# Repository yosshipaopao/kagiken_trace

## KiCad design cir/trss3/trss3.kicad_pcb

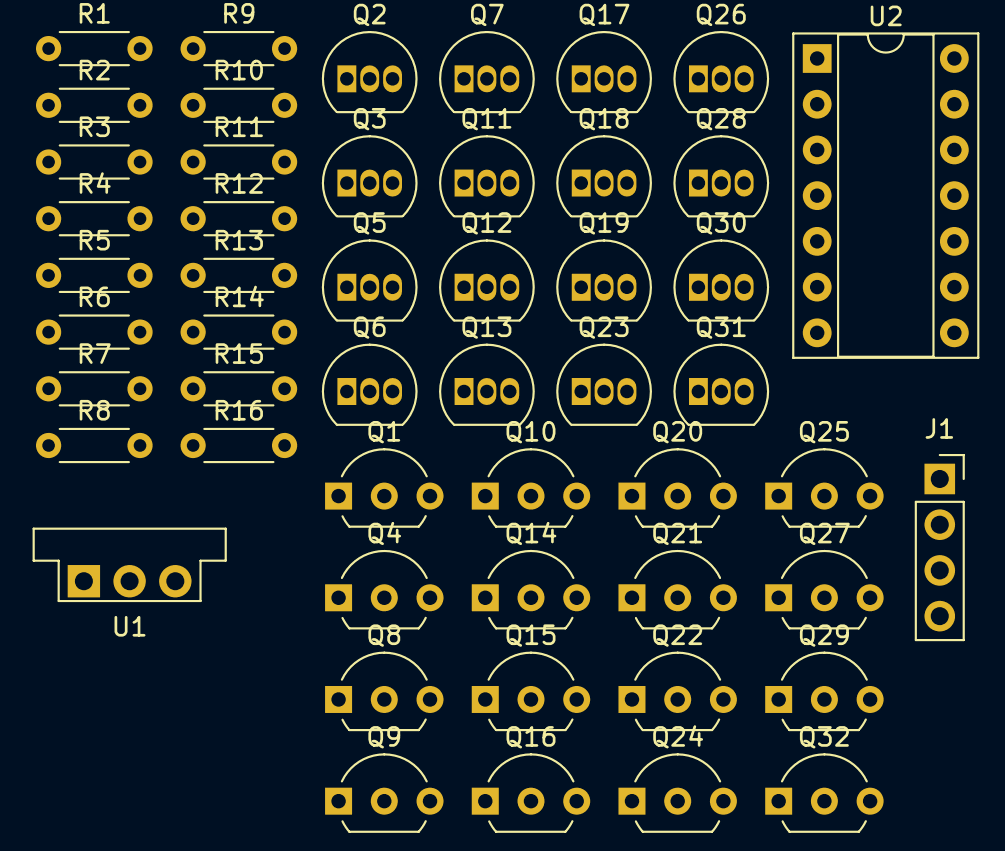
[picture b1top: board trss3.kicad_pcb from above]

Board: 2 copper layers, 51 parts (0 on the bottom side), 40 nets, no tracks yet.

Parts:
J1: Conn_01x04; PinSocket_1x04_P2.54mm_Vertical
Q1, Q4, Q8, Q9, Q10, Q14, Q15, Q16, Q20, Q21, Q22, Q24, Q25, Q27, Q29, Q32: 2SC1815; TO-92L_Inline_Wide
Q2, Q3, Q5, Q6, Q7, Q11, Q12, Q13, Q17, Q18, Q19, Q23, Q26, Q28, Q30, Q31: 2SA1015; TO-92_Inline
R1, R2, R3, R4, R5, R6, R7, R8: 10k; R_Axial_DIN0204_L3.6mm_D1.6mm_P5.08mm_Horizontal
R9, R10, R11, R12, R13, R14, R15, R16: 5.1k; R_Axial_DIN0204_L3.6mm_D1.6mm_P5.08mm_Horizontal
U1: OKI-78SR-12_1.0-W36-C; Converter_DCDC_Murata_OKI-78SR_Vertical
U2: 74LS07; DIP-14_W7.62mm_Socket

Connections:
+5V: Q2.2 (C), Q4.2 (C), Q5.2 (C), Q7.2 (C), Q9.2 (C), Q10.2 (C), Q11.2 (C), Q13.2 (C), Q16.2 (C), Q17.2 (C), Q19.2 (C), Q21.2 (C), Q22.2 (C), Q23.2 (C), Q25.2 (C), Q26.2 (C), Q29.2 (C), Q31.2 (C), U1.3 (OUT), U2.14 (VCC)
A: Q2.3 (B), Q7.3 (B), Q13.3 (B), Q21.3 (B), Q26.3 (B), Q32.3 (B), R9.1
A_IN: J1.1, U2.1
B: Q8.3 (B), Q11.3 (B), Q24.3 (B), Q28.3 (B), R10.1
B_IN: J1.2, U2.3
C: Q3.3 (B), Q14.3 (B), Q20.3 (B), Q30.3 (B), R11.1
C_IN: J1.3, U2.5
D: Q9.3 (B), Q12.3 (B), Q19.3 (B), Q23.3 (B), Q27.3 (B), Q31.3 (B), R12.1
D_IN: J1.4, U2.9
E: Q1.3 (B), Q5.3 (B), Q17.3 (B), Q27.1 (E), Q28.1 (E), R7.1
F: Q6.3 (B), Q15.3 (B), Q18.3 (B), Q30.1 (E), Q32.1 (E), R8.1
GND: R1.2, R2.2, R3.2, R4.2, R5.2, R6.2, R7.2, R8.2, U1.2 (GND), U2.7 (GND)
ML0: Q4.1 (E), Q6.1 (E), Q8.1 (E), Q9.1 (E), R2.1, R16.2
ML1: Q10.1 (E), Q14.1 (E), R3.1
MR0: Q16.1 (E), Q18.1 (E), Q20.1 (E), Q21.1 (E), R5.1, R15.2
MR1: Q22.1 (E), Q24.1 (E), R6.1
unnamed: Q1.2 (C), Q3.1 (E)
unnamed: Q1.1 (E), R1.1, R13.2
unnamed: Q2.1 (E), Q3.2 (C)
unnamed: Q5.1 (E), Q6.2 (C)
unnamed: Q7.1 (E), Q8.2 (C)
unnamed: Q10.3 (B), R16.1
unnamed: Q11.1 (E), Q12.2 (C)
unnamed: Q12.1 (E), Q15.2 (C)
unnamed: Q13.1 (E), Q14.2 (C)
unnamed: Q15.1 (E), R4.1, R14.2
unnamed: Q17.1 (E), Q18.2 (C)
unnamed: Q19.1 (E), Q20.2 (C)
unnamed: Q22.3 (B), R15.1
unnamed: Q23.1 (E), Q24.2 (C)
unnamed: Q25.1 (E), Q28.2 (C)
unnamed: Q26.1 (E), Q27.2 (C)
unnamed: Q29.1 (E), Q30.2 (C)
unnamed: Q31.1 (E), Q32.2 (C)
unnamed: R9.2, U2.2
unnamed: R10.2, U2.4
unnamed: R11.2, U2.6
unnamed: R12.2, U2.8
~A~CE: Q4.3 (B), Q25.3 (B), R13.1
~B~DF: Q16.3 (B), Q29.3 (B), R14.1

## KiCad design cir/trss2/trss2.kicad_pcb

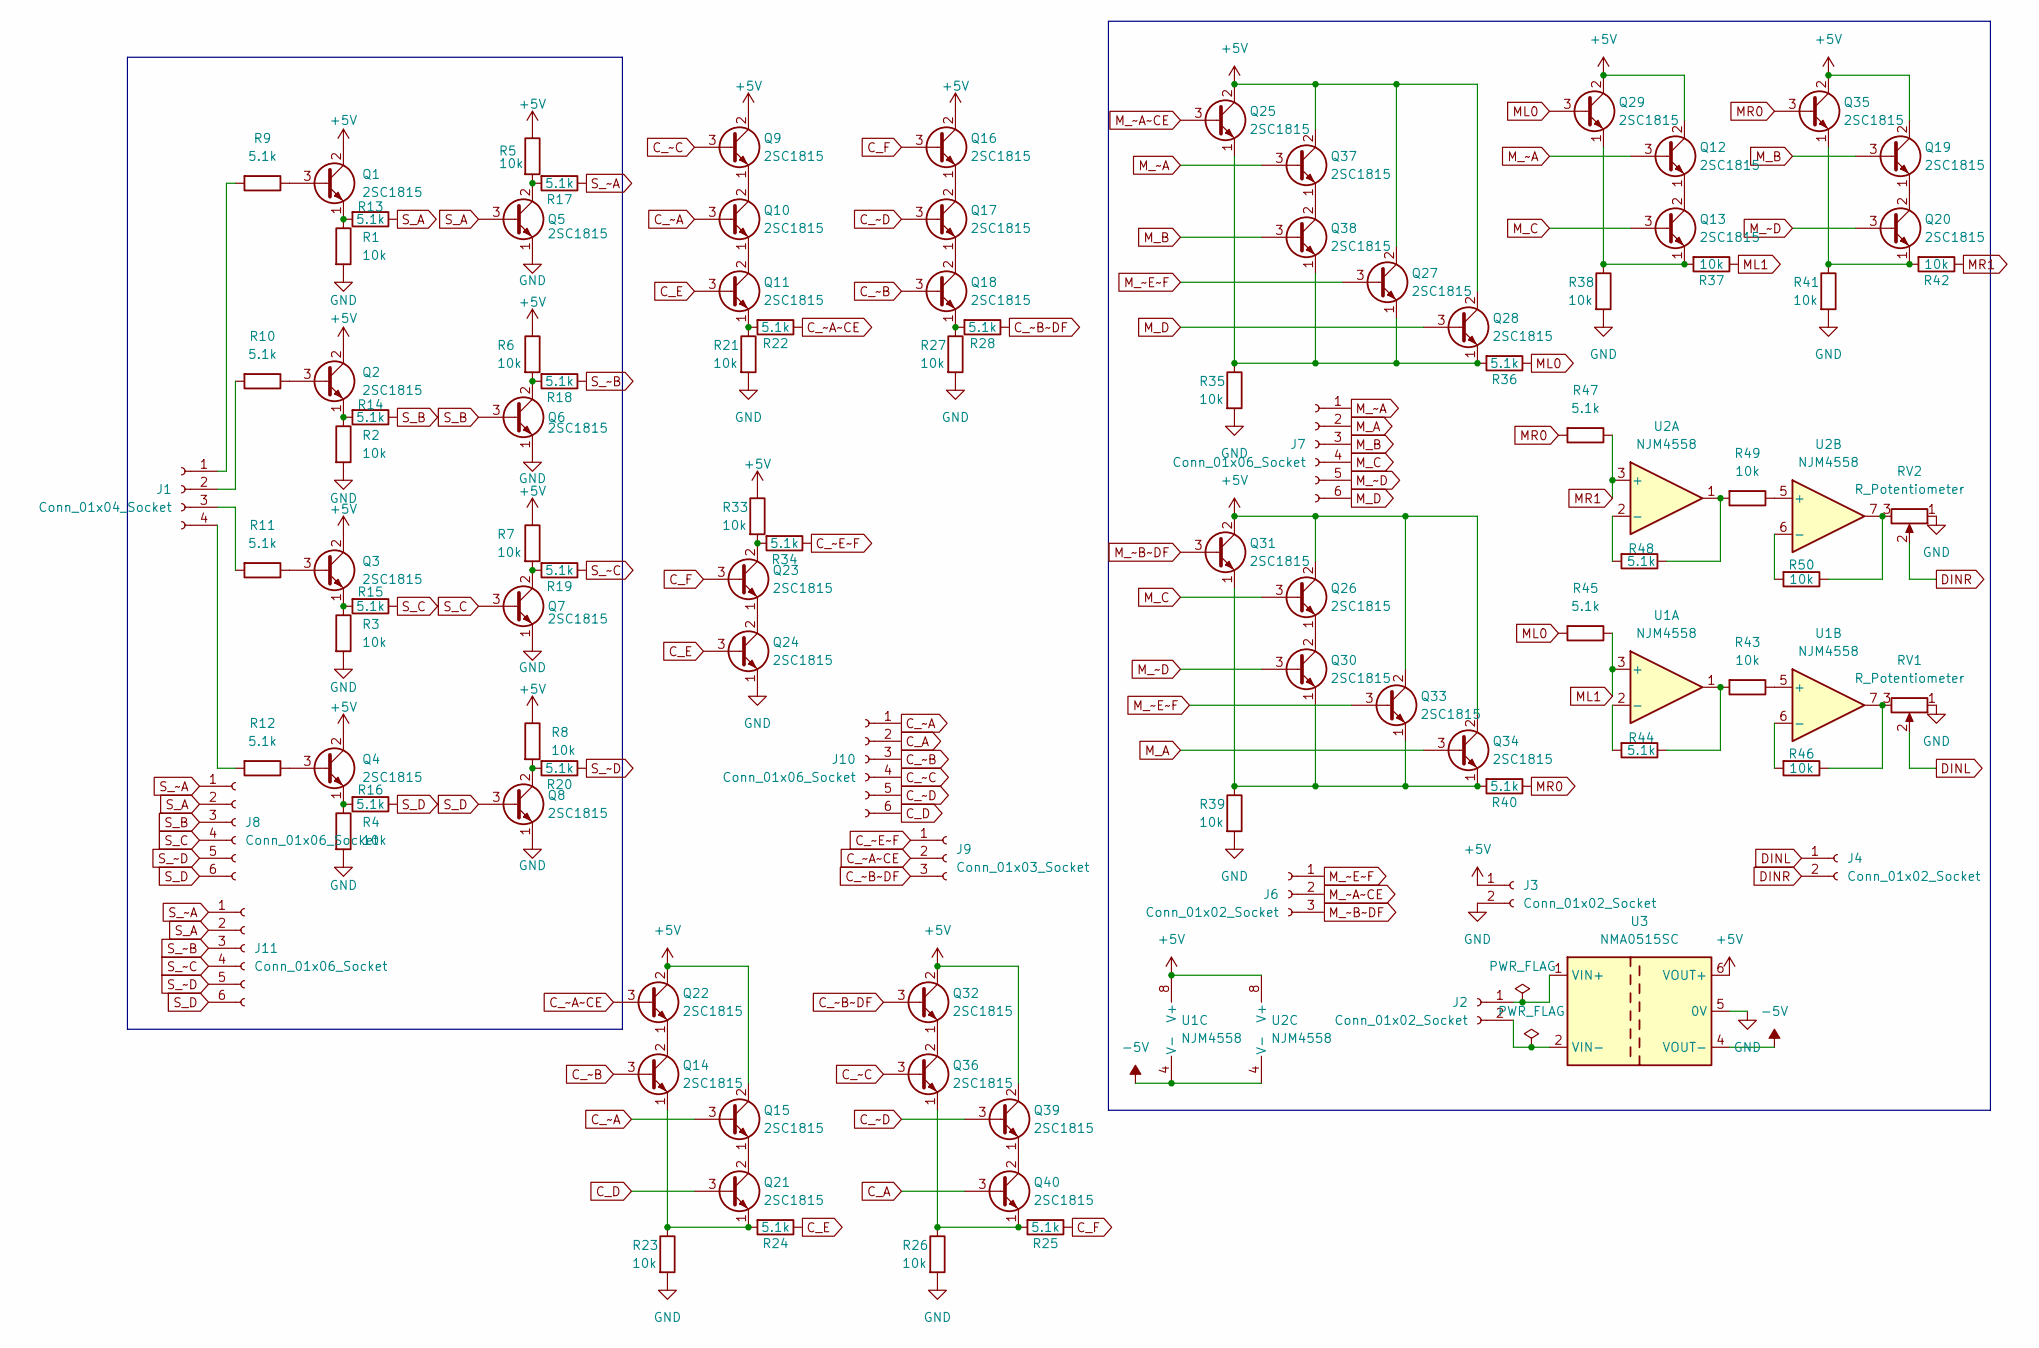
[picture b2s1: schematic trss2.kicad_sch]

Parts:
J1: Conn_01x04_Socket; PinSocket_1x04_P2.54mm_Vertical
J2, J3, J4: Conn_01x02_Socket; PinSocket_1x02_P2.54mm_Vertical
J6: Conn_01x02_Socket; PinSocket_1x03_P2.54mm_Vertical
J7, J8, J10, J11: Conn_01x06_Socket; PinSocket_1x06_P2.54mm_Vertical
J9: Conn_01x03_Socket; PinSocket_1x03_P2.54mm_Vertical
Q1, Q2, Q3, Q4, Q5, Q6, Q7, Q8, Q9, Q10, Q11, Q12, Q13, Q14, Q15, Q16, Q17, Q18, Q19, Q20, Q21, Q22, Q23, Q24, Q25, Q26, Q27, Q28, Q29, Q30, Q31, Q32, Q33, Q34, Q35, Q36, Q37, Q38, Q39, Q40: 2SC1815; TO-92_Inline_Wide
R1, R2, R3, R4, R5, R6, R7, R8, R21, R23, R26, R27, R33, R35, R37, R38, R39, R41, R42, R43, R46, R49, R50: 10k; R_Axial_DIN0204_L3.6mm_D1.6mm_P5.08mm_Horizontal
R9, R10, R11, R12, R17, R18, R19, R20, R22, R24, R25, R28, R34, R36, R40, R44, R45, R47, R48: 5.1k; R_Axial_DIN0204_L3.6mm_D1.6mm_P5.08mm_Horizontal
R13, R14, R15, R16: 5.1k; R_Axial_DIN0204_L3.6mm_D1.6mm_P7.62mm_Horizontal
RV1, RV2: R_Potentiometer; Potentiometer_Bourns_3296X_Horizontal
U1, U2: NJM4558; DIP-8_W7.62mm_Socket
U3: NMA0515SC; Converter_DCDC_Murata_NMAxxxxSC_THT

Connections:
+5V: J3.1, Q1.2 (C), Q2.2 (C), Q3.2 (C), Q4.2 (C), Q9.2 (C), Q12.2 (C), Q15.2 (C), Q16.2 (C), Q19.2 (C), Q22.2 (C), Q25.2 (C), Q26.2 (C), Q27.2 (C), Q28.2 (C), Q29.2 (C), Q31.2 (C), Q32.2 (C), Q33.2 (C), Q34.2 (C), Q35.2 (C), Q37.2 (C), Q39.2 (C), R5.1, R6.1, R7.1, R8.1, R33.1, U1.8 (V+), U2.8 (V+), U3.6 (VOUT+); also elsewhere on the board
-5V: U1.4 (V-), U2.4 (V-), U3.4 (VOUT-)
C_A: J10.2, Q40.3 (B); also elsewhere on the board
C_D: J10.6, Q21.3 (B); also elsewhere on the board
C_E: Q11.3 (B), Q24.3 (B), R24.1
C_F: Q16.3 (B), Q23.3 (B), R25.1
C_~A: J10.1, Q10.3 (B), Q15.3 (B); also elsewhere on the board
C_~A~CE: J9.2, Q22.3 (B), R22.1
C_~B: J10.3, Q14.3 (B), Q18.3 (B); also elsewhere on the board
C_~B~DF: J9.3, Q32.3 (B), R28.1
C_~C: J10.4, Q9.3 (B), Q36.3 (B); also elsewhere on the board
C_~D: J10.5, Q17.3 (B), Q39.3 (B); also elsewhere on the board
C_~E~F: J9.1, R34.1
DINL: J4.1, RV1.2
DINR: J4.2, RV2.2
GND: J3.2, Q5.1 (E), Q6.1 (E), Q7.1 (E), Q8.1 (E), Q24.1 (E), R1.2, R2.2, R3.2, R4.2, R21.2, R23.2, R26.2, R27.2, R35.2, R38.2, R39.2, R41.2, RV1.1, RV2.1, U3.5 (0V); also elsewhere on the board
ML0: Q29.3 (B), R36.1, R45.2
ML1: R37.1, R45.1, U1.3 (+)
MR0: Q35.3 (B), R40.1, R47.2
MR1: R42.1, R47.1, U2.3 (+)
M_A: J7.2, Q34.3 (B)
M_B: J7.3, Q19.3 (B), Q38.3 (B)
M_C: J7.4, Q13.3 (B), Q26.3 (B)
M_D: J7.6, Q28.3 (B)
M_~A: J7.1, Q12.3 (B), Q37.3 (B)
M_~A~CE: J6.2, Q25.3 (B)
M_~B~DF: J6.3, Q31.3 (B)
M_~D: J7.5, Q20.3 (B), Q30.3 (B)
M_~E~F: J6.1, Q27.3 (B), Q33.3 (B)
unnamed: J1.1, R9.2
unnamed: J1.2, R10.2
unnamed: J1.3, R11.2
unnamed: J1.4, R12.2
unnamed: J2.1, U3.1 (VIN+)
unnamed: J2.2, U3.2 (VIN-)
unnamed: Q1.3 (B), R9.1
unnamed: Q1.1 (E), R1.1, R13.2
unnamed: Q2.3 (B), R10.1
unnamed: Q2.1 (E), R2.1, R14.2
unnamed: Q3.3 (B), R11.1
unnamed: Q3.1 (E), R3.1, R15.2
unnamed: Q4.3 (B), R12.1
unnamed: Q4.1 (E), R4.1, R16.2
unnamed: Q5.2 (C), R5.2, R17.2
unnamed: Q6.2 (C), R6.2, R18.2
unnamed: Q7.2 (C), R7.2, R19.2
unnamed: Q8.2 (C), R8.2, R20.2
unnamed: Q9.1 (E), Q10.2 (C)
unnamed: Q10.1 (E), Q11.2 (C)
unnamed: Q11.1 (E), R21.1, R22.2
unnamed: Q12.1 (E), Q13.2 (C)
unnamed: Q13.1 (E), Q29.1 (E), R37.2, R38.1
unnamed: Q14.2 (C), Q22.1 (E)
unnamed: Q14.1 (E), Q21.1 (E), R23.1, R24.2
unnamed: Q15.1 (E), Q21.2 (C)
unnamed: Q16.1 (E), Q17.2 (C)
unnamed: Q17.1 (E), Q18.2 (C)
unnamed: Q18.1 (E), R27.1, R28.2
unnamed: Q19.1 (E), Q20.2 (C)
unnamed: Q20.1 (E), Q35.1 (E), R41.1, R42.2
unnamed: Q23.2 (C), R33.2, R34.2
unnamed: Q23.1 (E), Q24.2 (C)
unnamed: Q25.1 (E), Q27.1 (E), Q28.1 (E), Q38.1 (E), R35.1, R36.2
unnamed: Q26.1 (E), Q30.2 (C)
unnamed: Q30.1 (E), Q31.1 (E), Q33.1 (E), Q34.1 (E), R39.1, R40.2
unnamed: Q32.1 (E), Q36.2 (C)
unnamed: Q36.1 (E), Q40.1 (E), R25.2, R26.1
unnamed: Q37.1 (E), Q38.2 (C)
unnamed: Q39.1 (E), Q40.2 (C)
unnamed: R43.2, R44.1, U1.1
unnamed: R46.1, RV1.3, U1.7
unnamed: R48.1, R49.2, U2.1
unnamed: R50.1, RV2.3, U2.7
unnamed: R44.2, U1.2 (-)
unnamed: R43.1, U1.5 (+)
unnamed: R46.2, U1.6 (-)
unnamed: R48.2, U2.2 (-)
unnamed: R49.1, U2.5 (+)
unnamed: R50.2, U2.6 (-)
S_A: J8.2, J11.2, Q5.3 (B), R13.1
S_B: J8.3, Q6.3 (B), R14.1
S_C: J8.4, Q7.3 (B), R15.1
S_D: J8.6, J11.6, Q8.3 (B), R16.1
S_~A: J8.1, J11.1, R17.1
S_~B: J11.3, R18.1
S_~C: J11.4, R19.1
S_~D: J8.5, J11.5, R20.1

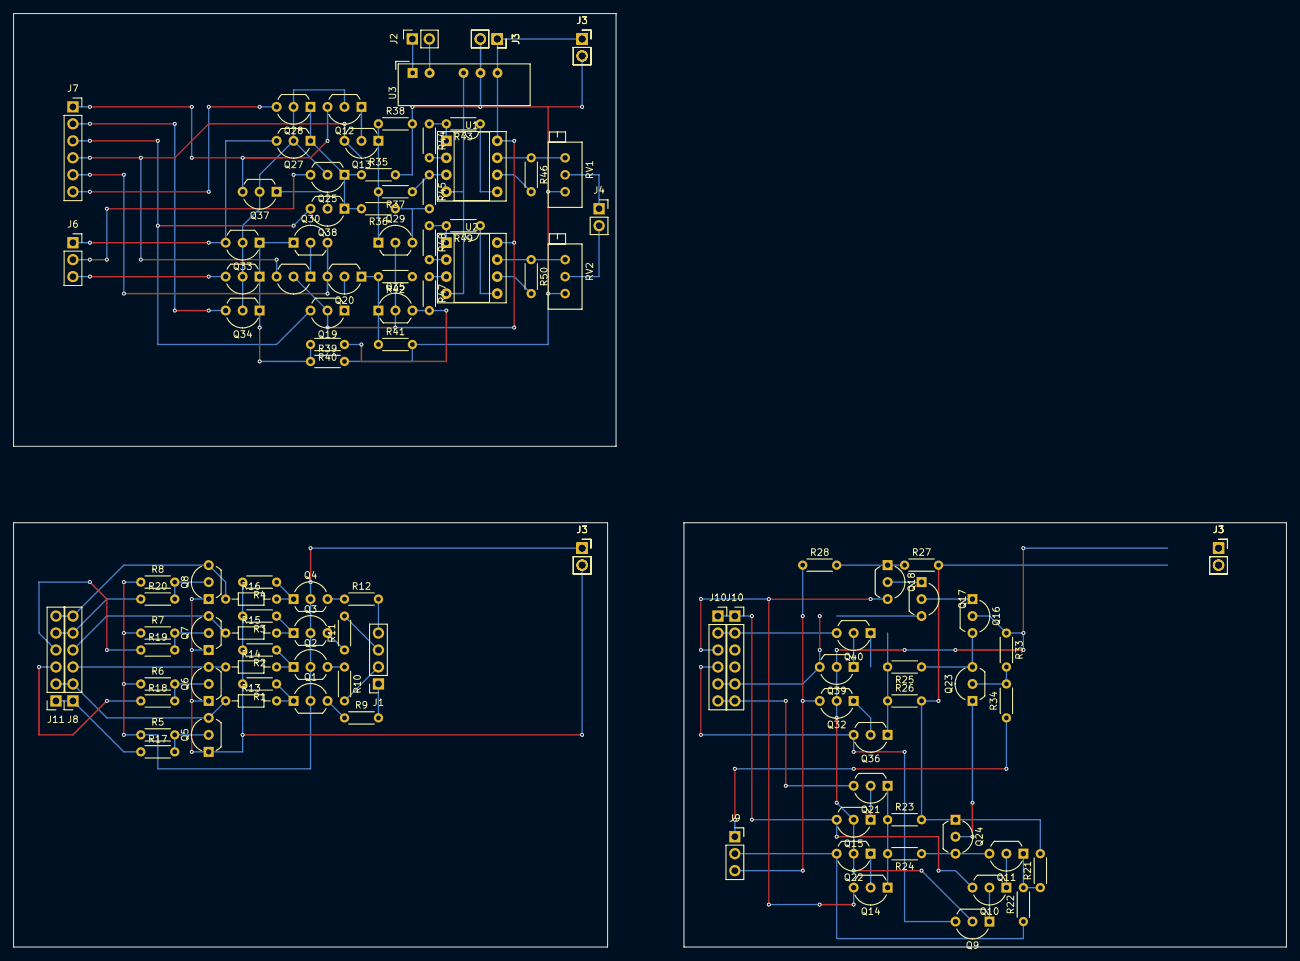
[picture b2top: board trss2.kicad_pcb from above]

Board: 2 copper layers, 190.5 x 139.7 mm, 109 parts (0 on the bottom side), 87 nets.

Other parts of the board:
J3#2, J3#3, J3#4, J3#5, J3#6, J3#7, J3#8: Conn_01x02_Socket; PinSocket_1x02_P2.54mm_Vertical
J10#2: Conn_01x06_Socket; PinSocket_1x06_P2.54mm_Vertical

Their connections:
+5V: J3#2.1, J3#3.1, J3#4.1, J3#5.1, J3#6.1, J3#7.1, J3#8.1; also elsewhere on the board
C_A: J10#2.2; also elsewhere on the board
C_D: J10#2.6; also elsewhere on the board
C_~A: J10#2.1; also elsewhere on the board
C_~B: J10#2.3; also elsewhere on the board
C_~C: J10#2.4; also elsewhere on the board
C_~D: J10#2.5; also elsewhere on the board
GND: J3#2.2, J3#3.2, J3#4.2, J3#5.2, J3#6.2, J3#7.2, J3#8.2; also elsewhere on the board

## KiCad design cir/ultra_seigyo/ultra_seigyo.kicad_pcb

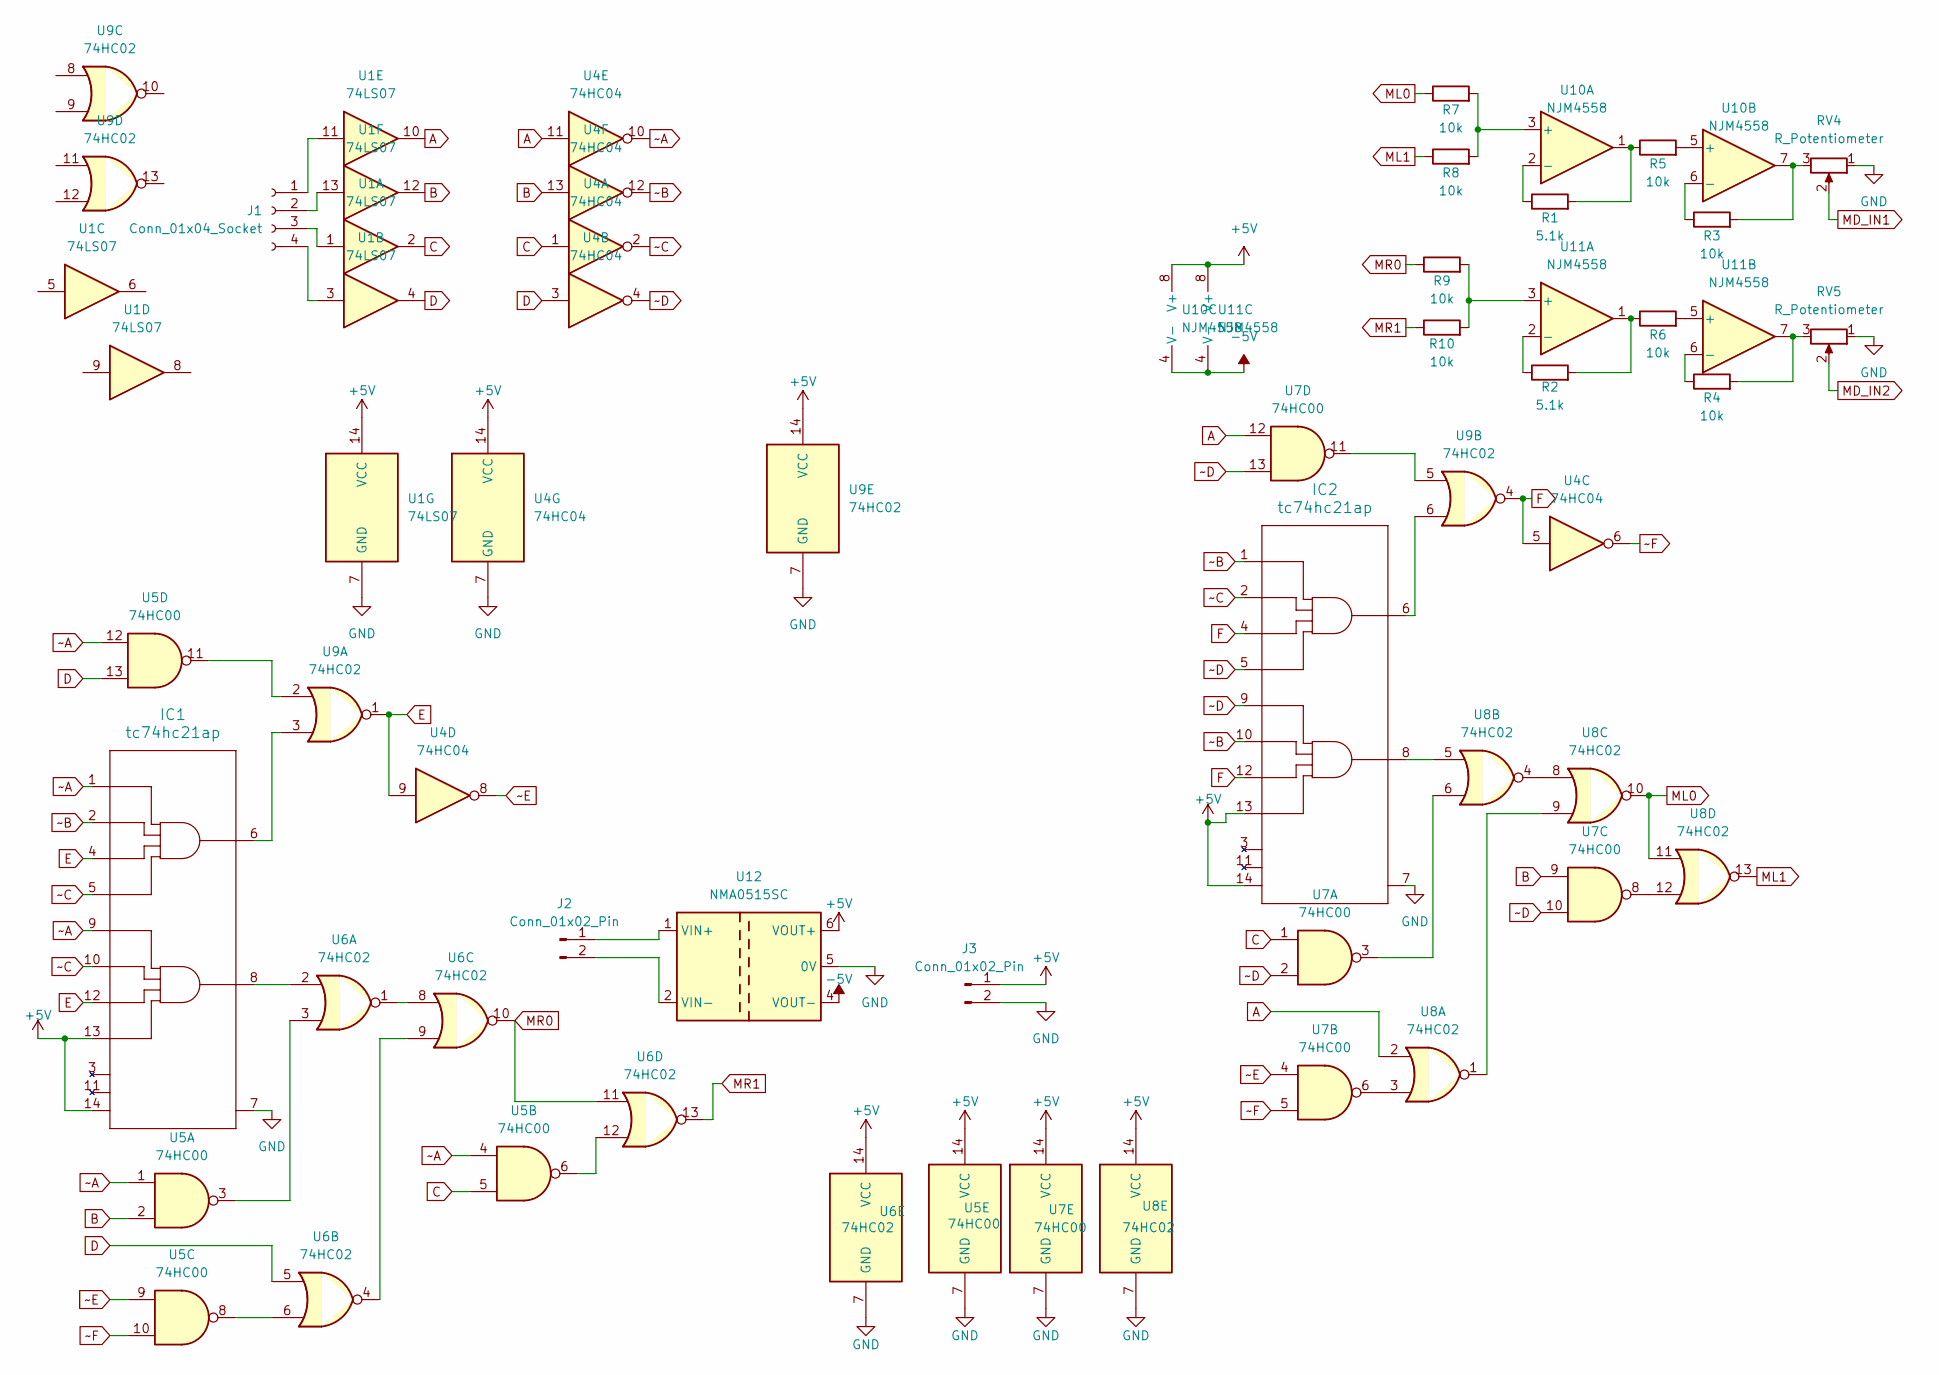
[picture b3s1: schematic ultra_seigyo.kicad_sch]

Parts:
IC1, IC2: tc74hc21ap; DIP-14_W7.62mm_Socket
J1: Conn_01x04_Socket; PinSocket_1x04_P2.54mm_Vertical
J2, J3: Conn_01x02_Pin; PinSocket_1x02_P2.54mm_Vertical
R1, R2: 5.1k; R_Axial_DIN0204_L3.6mm_D1.6mm_P5.08mm_Horizontal
R3, R4, R5, R6, R7, R8, R9, R10: 10k; R_Axial_DIN0204_L3.6mm_D1.6mm_P5.08mm_Horizontal
RV4, RV5: R_Potentiometer; Potentiometer_Bourns_3296X_Horizontal
U1: 74LS07; DIP-14_W7.62mm_Socket
U4: 74HC04; DIP-14_W7.62mm_Socket
U5, U7: 74HC00; DIP-14_W7.62mm_Socket
U6, U8, U9: 74HC02; DIP-14_W7.62mm_Socket
U10, U11: NJM4558; DIP-8_W7.62mm_Socket
U12: NMA0515SC; Converter_DCDC_Murata_NMAxxxxSC_THT

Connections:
+5V: IC1.13, IC1.14, IC2.13, IC2.14, J3.1, U1.14 (VCC), U4.14 (VCC), U5.14 (VCC), U6.14 (VCC), U7.14 (VCC), U8.14 (VCC), U9.14 (VCC), U10.8 (V+), U11.8 (V+), U12.6 (VOUT+)
-5V: U10.4 (V-), U11.4 (V-), U12.4 (VOUT-)
A: U1.10, U4.11, U7.12, U8.2
B: U1.12, U4.13, U5.2, U7.9
C: U1.2, U4.1, U5.5, U7.1
D: U1.4, U4.3, U5.13, U6.5
E: IC1.4, IC1.12, U4.9, U9.1
F: IC2.4, IC2.12, U4.5, U9.4
GND: IC1.7, IC2.7, J3.2, RV4.1, RV5.1, U1.7 (GND), U4.7 (GND), U5.7 (GND), U6.7 (GND), U7.7 (GND), U8.7 (GND), U9.7 (GND), U12.5 (0V)
MD_IN1: RV4.2
MD_IN2: RV5.2
ML0: R7.1, U8.10, U8.11
ML1: R8.1, U8.13
MR0: R9.1, U6.10, U6.11
MR1: R10.1, U6.13
unnamed: IC1.6, U9.3
unnamed: IC1.8, U6.2
unnamed: IC2.6, U9.6
unnamed: IC2.8, U8.5
unnamed: J1.1, U1.11
unnamed: J1.2, U1.13
unnamed: J1.3, U1.1
unnamed: J1.4, U1.3
unnamed: J2.1, U12.1 (VIN+)
unnamed: J2.2, U12.2 (VIN-)
unnamed: R1.2, R5.1, U10.1
unnamed: R2.2, R6.1, U11.1
unnamed: R3.2, RV4.3, U10.7
unnamed: R4.2, RV5.3, U11.7
unnamed: U5.3, U6.3
unnamed: U5.6, U6.12
unnamed: U5.8, U6.6
unnamed: U5.11, U9.2
unnamed: U6.1, U6.8
unnamed: U6.4, U6.9
unnamed: U7.3, U8.6
unnamed: U7.6, U8.3
unnamed: U7.8, U8.12
unnamed: U7.11, U9.5
unnamed: U8.1, U8.9
unnamed: U8.4, U8.8
unnamed: R7.2, R8.2, U10.3 (+)
unnamed: R1.1, U10.2 (-)
unnamed: R5.2, U10.5 (+)
unnamed: R3.1, U10.6 (-)
unnamed: R9.2, R10.2, U11.3 (+)
unnamed: R2.1, U11.2 (-)
unnamed: R6.2, U11.5 (+)
unnamed: R4.1, U11.6 (-)
~A: IC1.1, IC1.9, U4.10, U5.1, U5.4, U5.12
~B: IC1.2, IC2.1, IC2.10, U4.12
~C: IC1.5, IC1.10, IC2.2, U4.2
~D: IC2.5, IC2.9, U4.4, U7.2, U7.10, U7.13
~E: U4.8, U5.9, U7.4
~F: U4.6, U5.10, U7.5

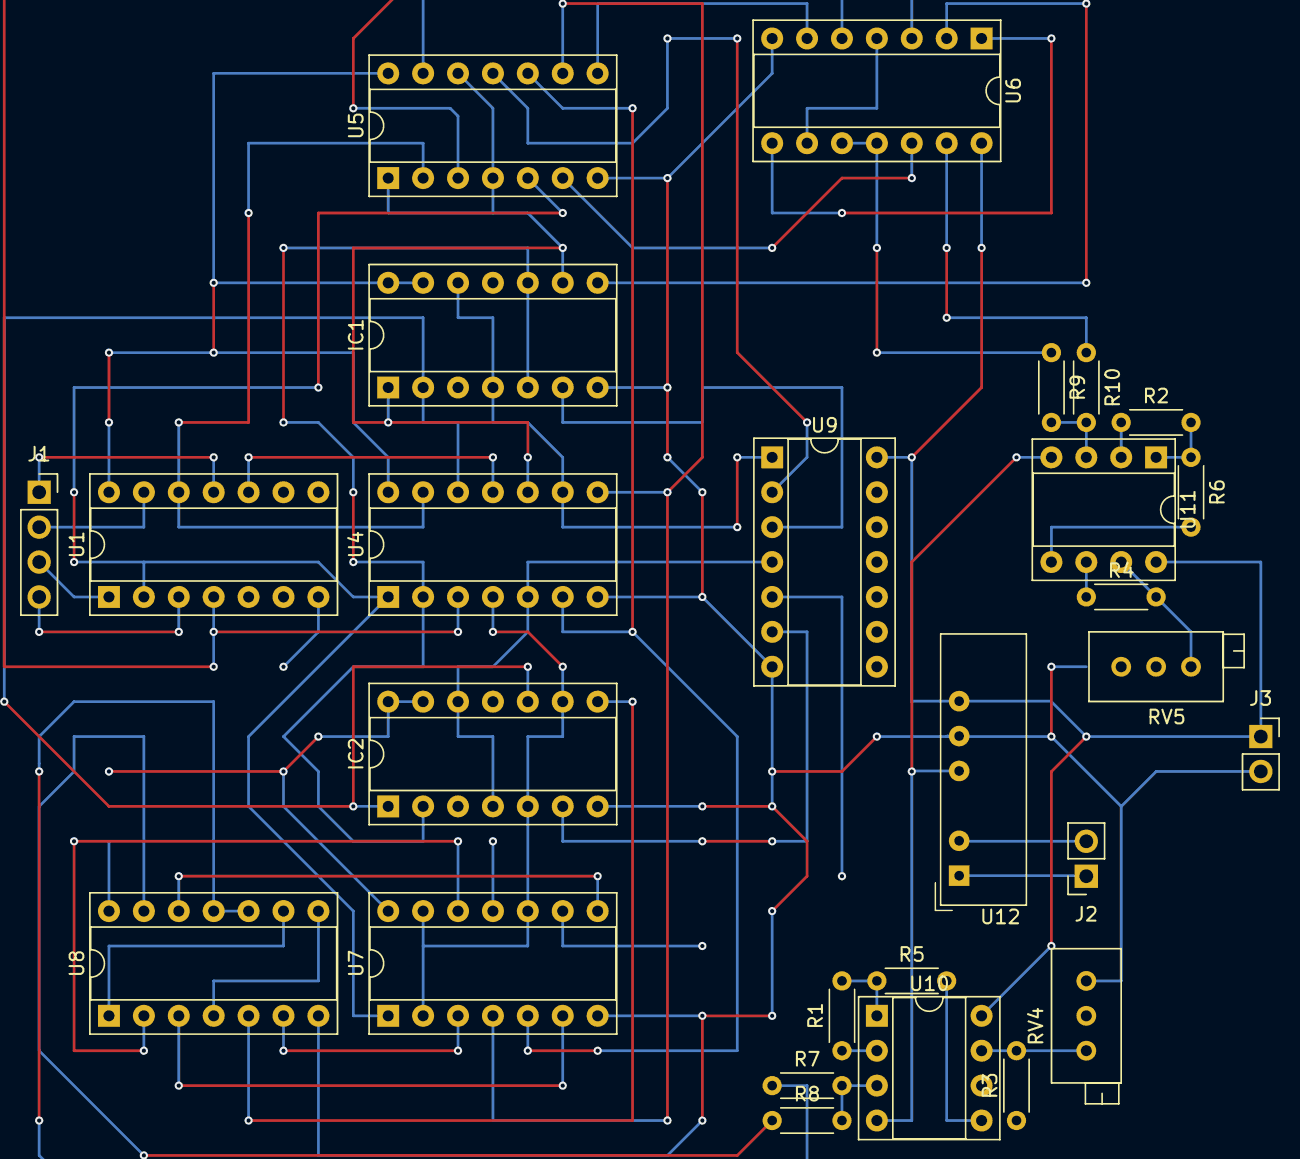
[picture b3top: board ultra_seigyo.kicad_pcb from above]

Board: 4 copper layers, 27 parts (0 on the bottom side), 53 nets.

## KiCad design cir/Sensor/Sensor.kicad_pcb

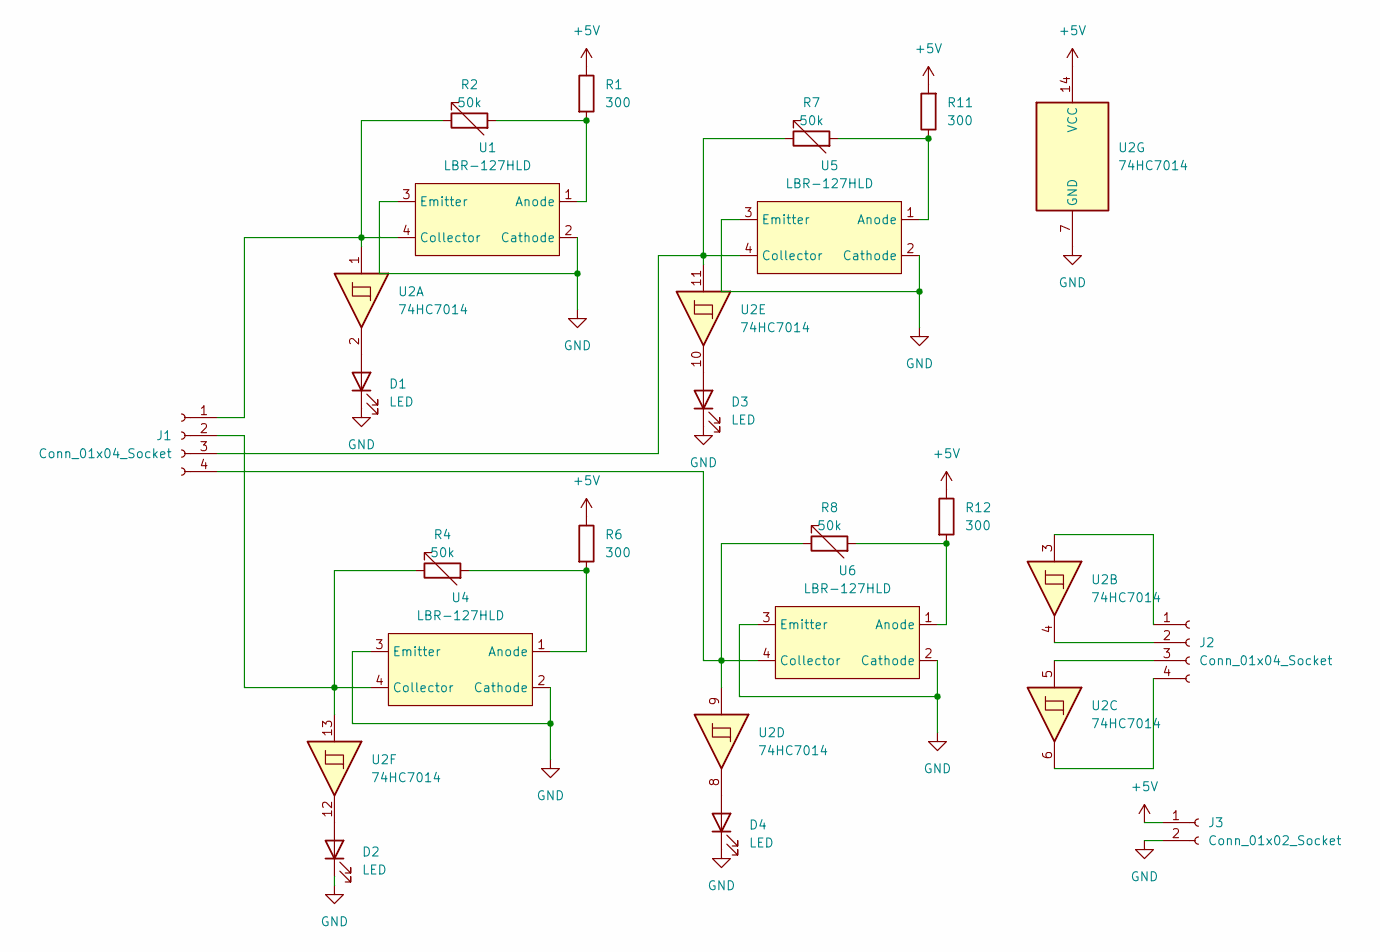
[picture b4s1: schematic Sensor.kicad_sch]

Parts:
D1, D2, D3, D4: LED; LED_D3.0mm
J1, J2: Conn_01x04_Socket; PinHeader_1x04_P2.54mm_Vertical
J3: Conn_01x02_Socket; PinHeader_1x02_P2.54mm_Vertical
R1, R6, R11, R12: 300; R_Axial_DIN0204_L3.6mm_D1.6mm_P5.08mm_Horizontal
R2, R4, R7, R8: 50k; Potentiometer_Bourns_3386P_Vertical
U1, U4, U5, U6: LBR-127HLD
U2: 74HC7014; DIP-14_W7.62mm_Socket

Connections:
+5V: J3.1, R1.1, R6.1, R11.2, R12.1, U2.14 (VCC)
GND: D1.1 (K), D2.1 (K), D3.1 (K), D4.1 (K), J3.2, U1.2 (Cathode), U1.3 (Emitter), U2.7 (GND), U4.2 (Cathode), U4.3 (Emitter), U5.2 (Cathode), U5.3 (Emitter), U6.2 (Cathode), U6.3 (Emitter)
unnamed: D1.2 (A), U2.2
unnamed: D2.2 (A), U2.12
unnamed: D3.2 (A), U2.10
unnamed: D4.2 (A), U2.8
unnamed: J1.1, R2.1, U1.4 (Collector), U2.1
unnamed: J1.2, R4.1, U2.13, U4.4 (Collector)
unnamed: J1.3, R7.1, U2.11, U5.4 (Collector)
unnamed: J1.4, R8.1, U2.9, U6.4 (Collector)
unnamed: J2.1, U2.3
unnamed: J2.2, U2.4
unnamed: J2.3, U2.5
unnamed: J2.4, U2.6
unnamed: R1.2, R2.2, U1.1 (Anode)
unnamed: R4.2, R6.2, U4.1 (Anode)
unnamed: R7.2, R11.1, U5.1 (Anode)
unnamed: R8.2, R12.2, U6.1 (Anode)

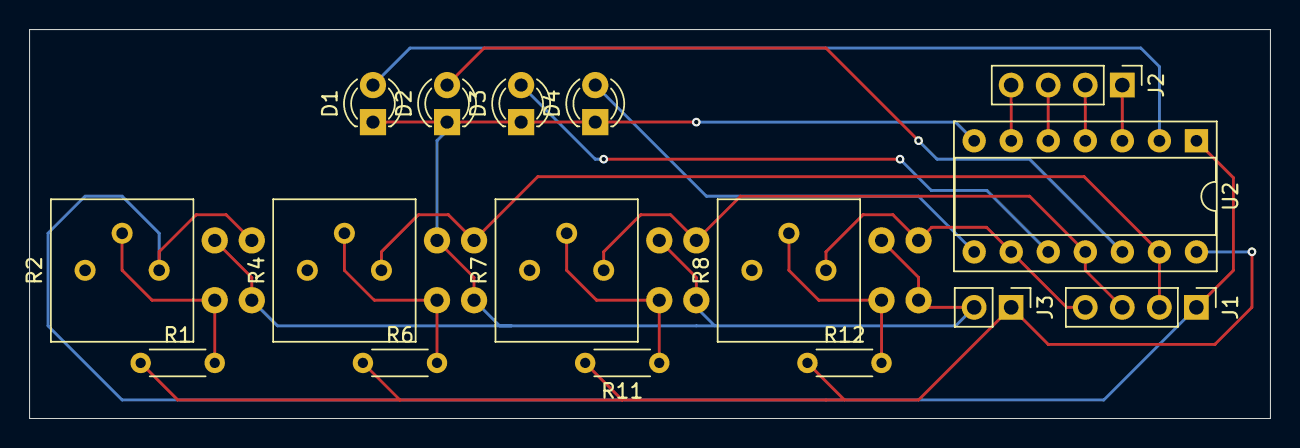
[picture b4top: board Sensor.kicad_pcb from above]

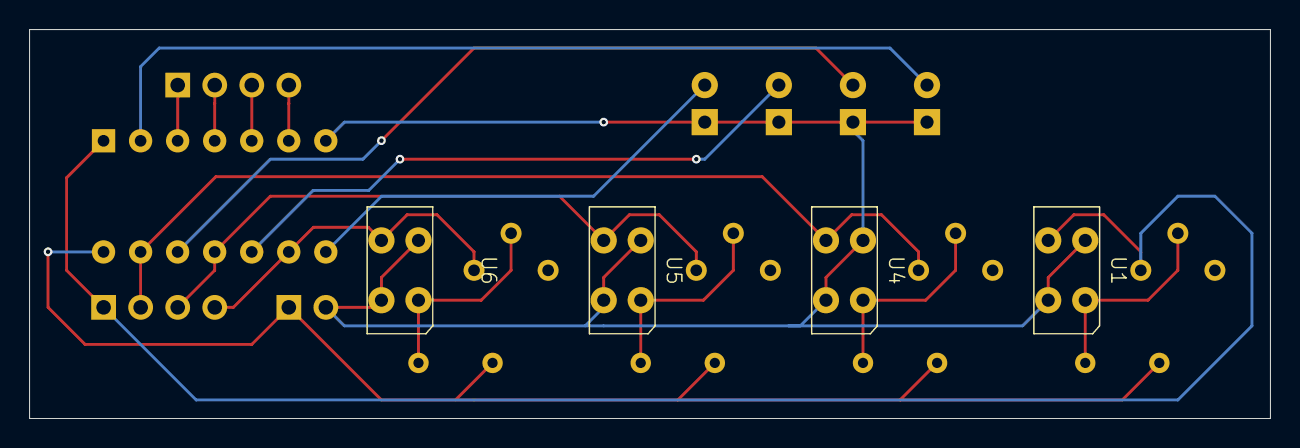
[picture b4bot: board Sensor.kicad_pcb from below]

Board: 2 copper layers, 85.1 x 26.7 mm, 20 parts (4 on the bottom side), 18 nets.

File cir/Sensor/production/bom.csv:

Designator,Footprint,Quantity,Value,LCSC Part #
"D1, D2, D3, D4",LED_D3.0mm,4,LED,
"J1, J2",PinHeader_1x04_P2.54mm_Vertical,2,Conn_01x04_Socket,
J3,PinHeader_1x02_P2.54mm_Vertical,1,Conn_01x02_Socket,
R1,R_Axial_DIN0204_L3.6mm_D1.6mm_P5.08mm_Horizontal,1,300,C3036833
"R10, R11, R12, R3, R5, R6, R9",R_Axial_DIN0204_L3.6mm_D1.6mm_P5.08mm_Horizontal,7,300,
"R2, R4, R7, R8",R_Variable,4,50k,
"U1, U4, U5, U6",LBR-127HLD,4,LBR-127HLD,
U2,DIP-14_W7.62mm_Socket,1,74HC7014,

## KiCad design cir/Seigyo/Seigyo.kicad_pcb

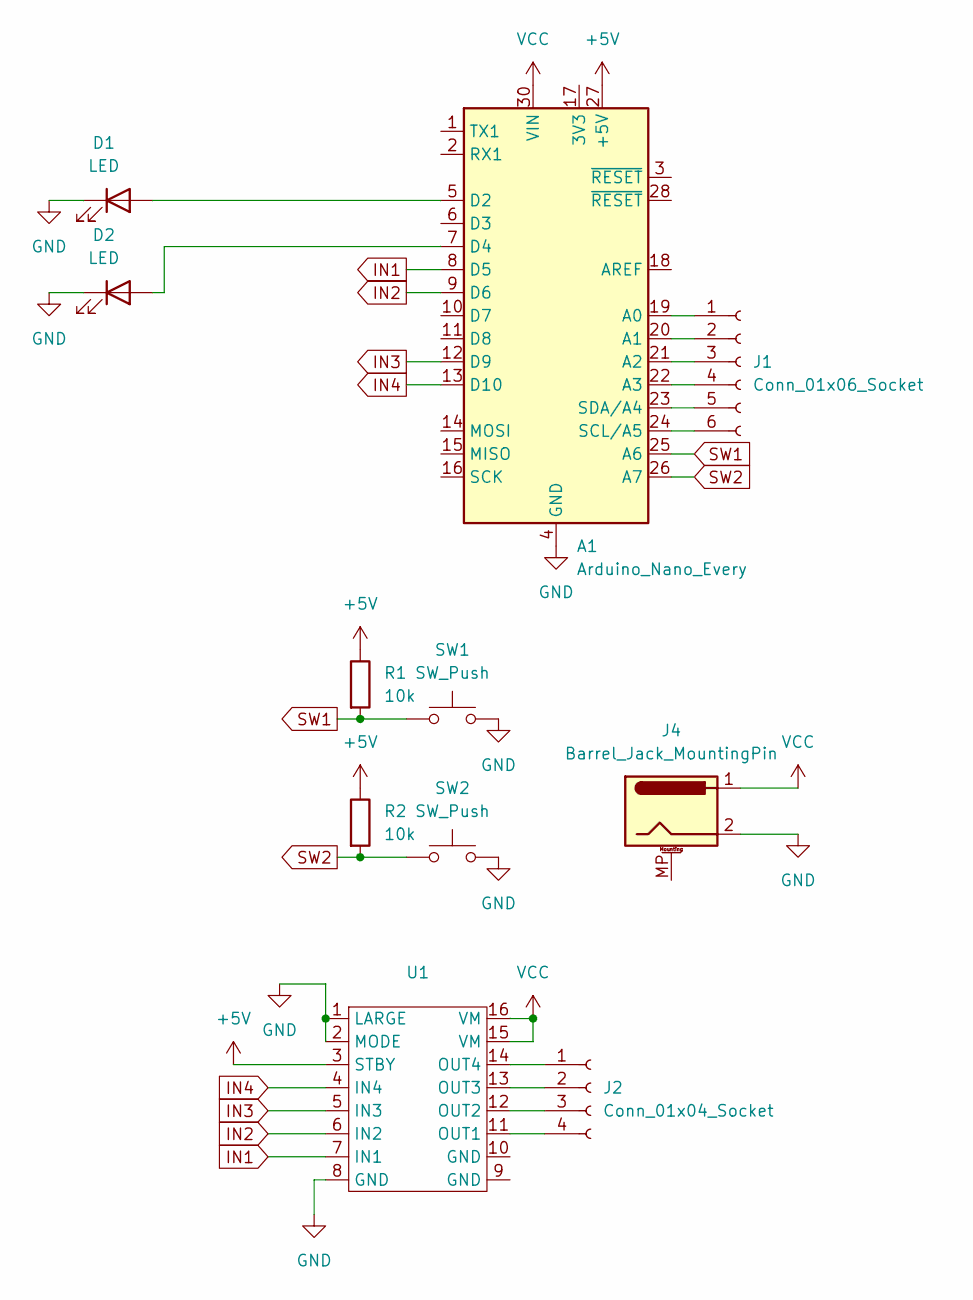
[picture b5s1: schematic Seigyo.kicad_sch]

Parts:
A1: Arduino_Nano_Every; Arduino_Nano
D1, D2: LED; LED_D3.0mm
J1: Conn_01x06_Socket; PinSocket_1x06_P2.54mm_Vertical
J2: Conn_01x04_Socket; PinSocket_1x04_P2.54mm_Vertical
J4: Barrel_Jack_MountingPin; BarrelJack_Horizontal
R1, R2: 10k; R_Axial_DIN0204_L3.6mm_D1.6mm_P5.08mm_Horizontal
SW1, SW2: SW_Push; SW
U1: TC78H6353FTG

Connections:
+5V: A1.27 (+5V), R1.1, R2.1, U1.3 (STBY)
GND: A1.4 (GND), A1.29 (GND), D1.1 (K), D2.1 (K), J4.2, SW1.2, SW2.2, U1.1 (LARGE), U1.2 (MODE), U1.8 (GND)
IN1: A1.8 (D5), U1.7 (IN1)
IN2: A1.9 (D6), U1.6 (IN2)
IN3: A1.12 (D9), U1.5 (IN3)
IN4: A1.13 (D10), U1.4 (IN4)
unnamed: A1.19 (A0), J1.1
unnamed: A1.20 (A1), J1.2
unnamed: A1.21 (A2), J1.3
unnamed: A1.22 (A3), J1.4
unnamed: A1.5 (D2), D1.2 (A)
unnamed: A1.7 (D4), D2.2 (A)
unnamed: A1.24 (SCL/A5), J1.6
unnamed: A1.23 (SDA/A4), J1.5
unnamed: J2.1, U1.14 (OUT4)
unnamed: J2.2, U1.13 (OUT3)
unnamed: J2.3, U1.12 (OUT2)
unnamed: J2.4, U1.11 (OUT1)
SW1: A1.25 (A6), R1.2, SW1.1
SW2: A1.26 (A7), R2.2, SW2.1
VCC: A1.30 (VIN), J4.1, U1.15 (VM), U1.16 (VM)

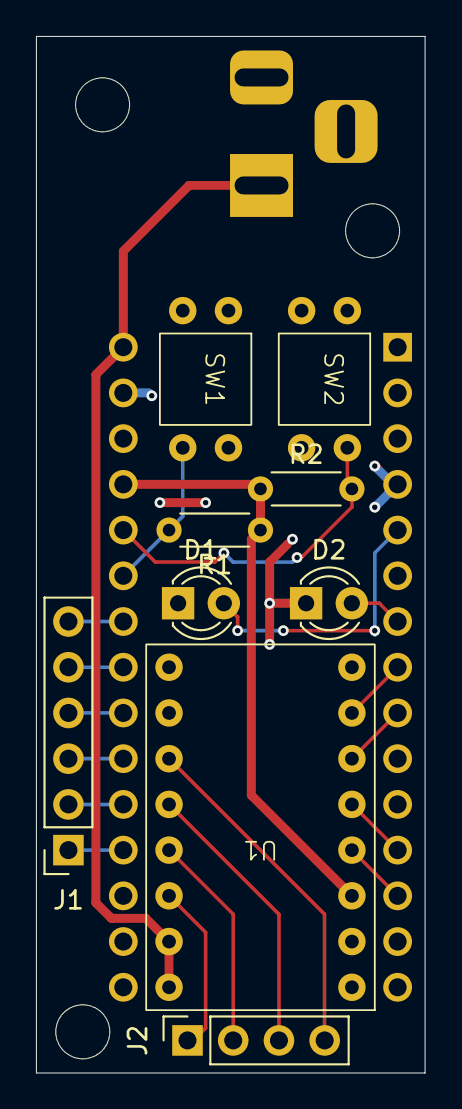
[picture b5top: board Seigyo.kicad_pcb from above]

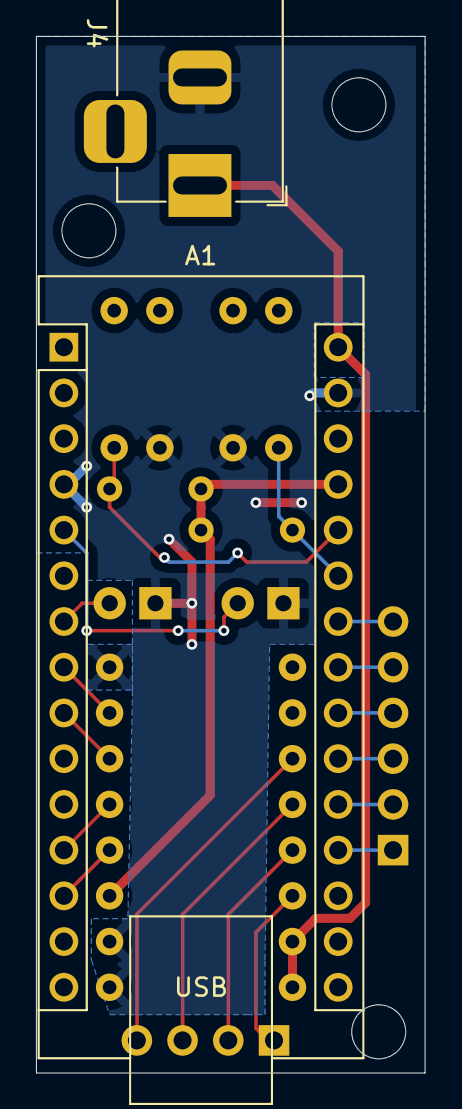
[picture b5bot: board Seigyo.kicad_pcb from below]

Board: 2 copper layers, 21.6 x 57.6 mm, 11 parts (2 on the bottom side), 21 nets.

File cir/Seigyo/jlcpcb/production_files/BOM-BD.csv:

Comment,Designator,Footprint,LCSC
Conn_01x04_Socket,J2,PinSocket_1x04_P2.54mm_Vertical,
SW_Push,SW1,SW,
10k,R2,R_Axial_DIN0204_L3.6mm_D1.6mm_P5.08mm_Horizontal,
~,U1,TC78H6353FTG,
LED,D2,LED_D3.0mm,
SW_Push,SW2,SW,
10k,R1,R_Axial_DIN0204_L3.6mm_D1.6mm_P5.08mm_Horizontal,
LED,D1,LED_D3.0mm,
Conn_01x06_Socket,J1,PinSocket_1x06_P2.54mm_Vertical,
Arduino_Nano_Every,A1,Arduino_Nano,
Barrel_Jack_MountingPin,J4,BarrelJack_Horizontal,
